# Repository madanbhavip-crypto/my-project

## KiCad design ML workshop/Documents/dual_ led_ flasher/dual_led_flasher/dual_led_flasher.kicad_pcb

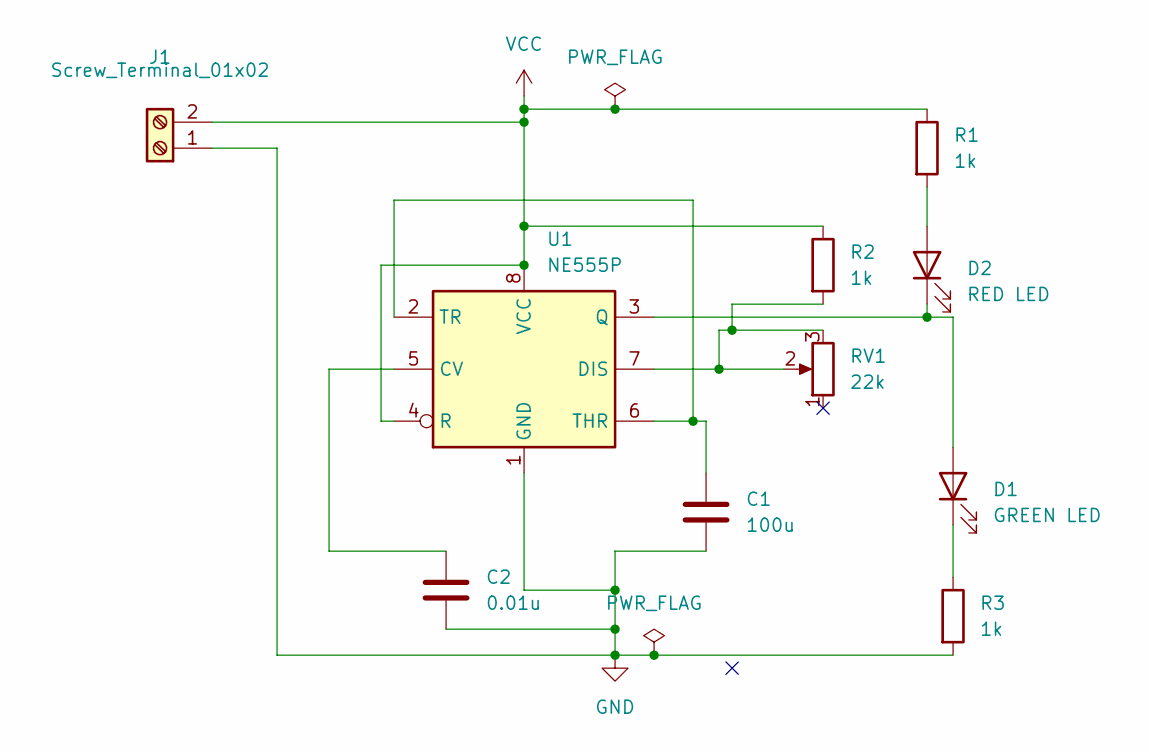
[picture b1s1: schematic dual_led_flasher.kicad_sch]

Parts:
C1: 100u; CP_Radial_D8.0mm_P3.80mm
C2: 0.01u; C_Disc_D3.8mm_W2.6mm_P2.50mm
D1: GREEN LED; LED_D5.0mm
D2: RED LED; LED_D5.0mm
J1: Screw_Terminal_01x02; TerminalBlock_MaiXu_MX126-5.0-02P_1x02_P5.00mm
R1, R2, R3: 1k; R_Axial_DIN0411_L9.9mm_D3.6mm_P12.70mm_Horizontal
RV1: 22k; Potentiometer_Bourns_3296W_Vertical
U1: NE555P; DIP-8_W7.62mm

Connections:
GND: C1.2, C2.2, J1.1, R3.2, U1.1 (GND)
unnamed: D1.2 (A), D2.1 (K), U1.3 (Q)
unnamed: D1.1 (K), R3.1
unnamed: D2.2 (A), R1.2
unnamed: C2.1, U1.5 (CV)
unnamed: R2.2, RV1.2, RV1.3, U1.7 (DIS)
unnamed: C1.1, U1.2 (TR), U1.6 (THR)
VCC: J1.2, R1.1, R2.1, U1.4 (R), U1.8 (VCC)

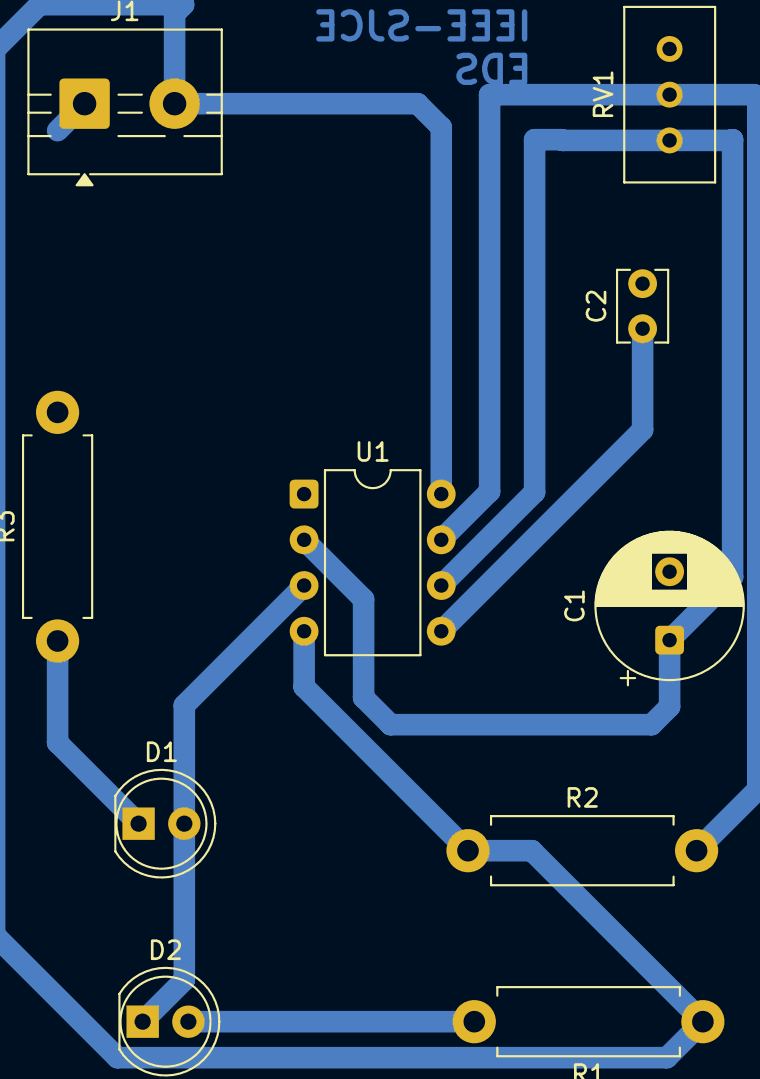
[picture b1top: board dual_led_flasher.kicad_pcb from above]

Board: 2 copper layers, 10 parts (0 on the bottom side), 8 nets.

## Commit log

2026-06-10 my first upload
2026-06-10 keep only magic-spells
